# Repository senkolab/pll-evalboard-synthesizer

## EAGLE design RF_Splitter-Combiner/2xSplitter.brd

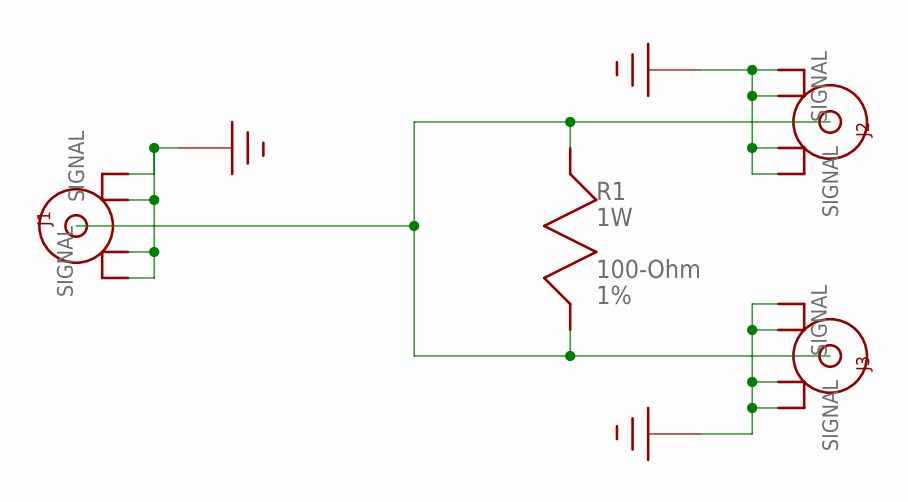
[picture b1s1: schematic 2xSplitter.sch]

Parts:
J1, J2, J3: SMA-END
R1: 100-Ohm; R1206

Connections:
GROUND: J1.P$2, J1.P$3, J1.P$4, J1.P$5, J2.P$2, J2.P$3, J2.P$4, J2.P$5, J3.P$2, J3.P$3, J3.P$4, J3.P$5
unnamed: J1.SIGNAL, J2.SIGNAL, J3.SIGNAL, R1.P$1 (A), R1.P$2 (B)

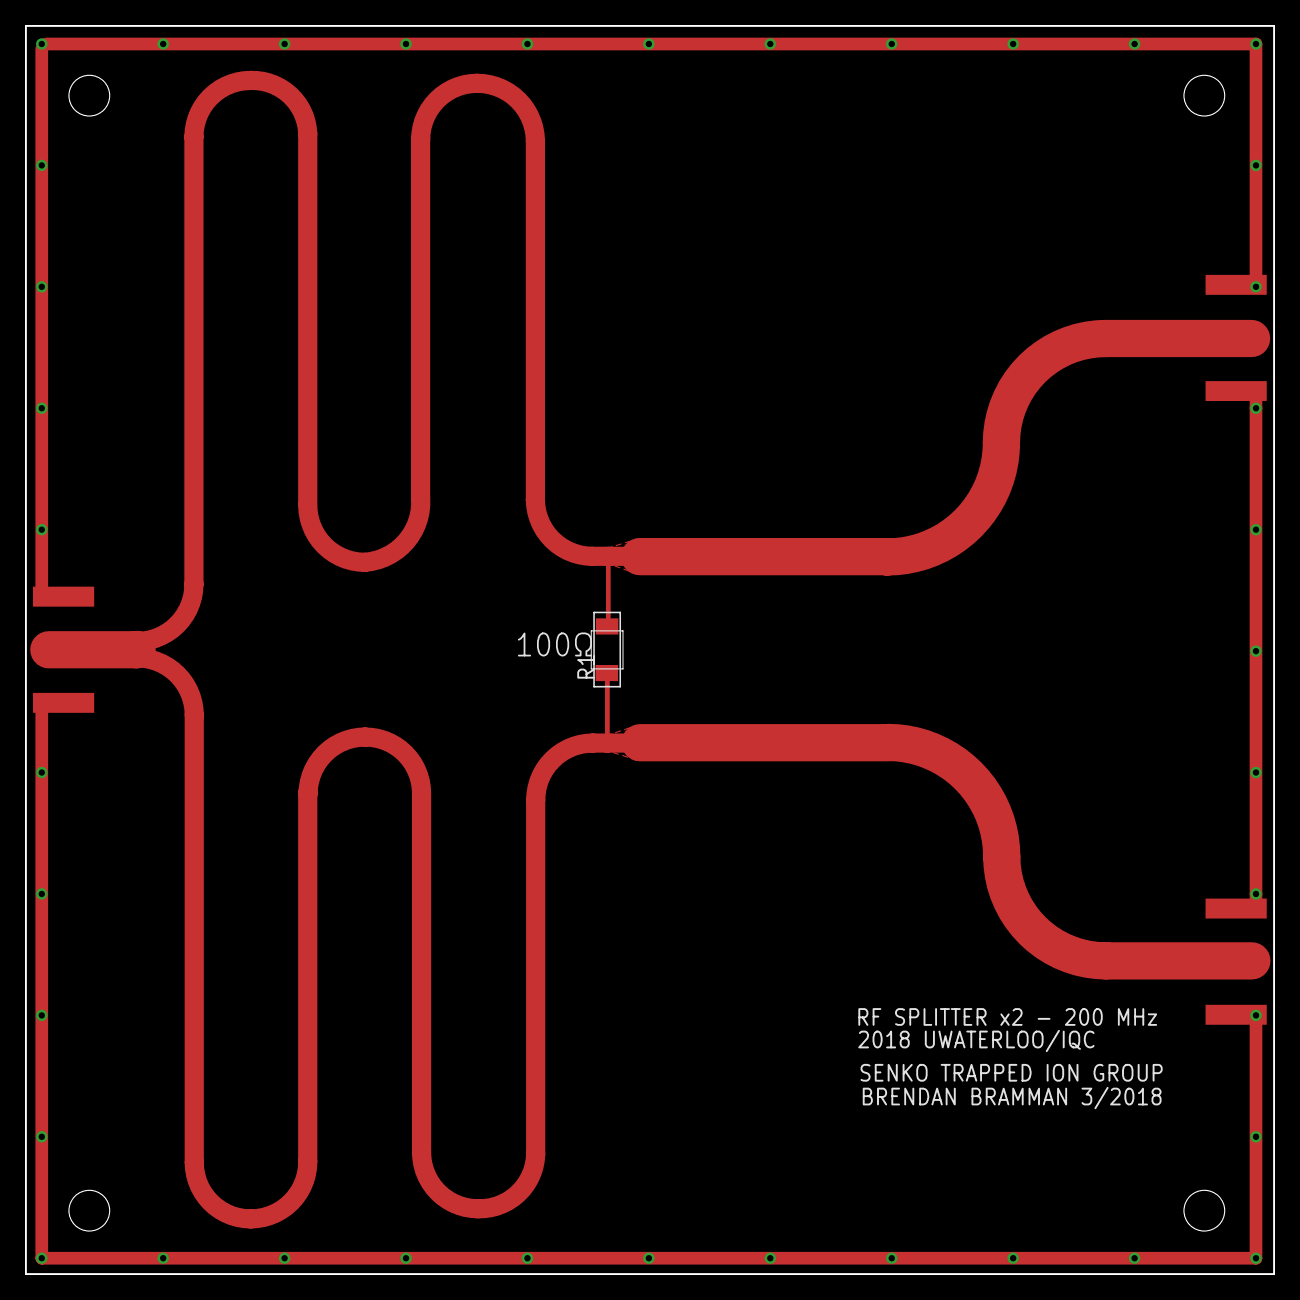
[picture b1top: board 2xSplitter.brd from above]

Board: 2 copper layers, 100.0 x 100.0 mm, 4 parts (0 on the bottom side), 2 nets.

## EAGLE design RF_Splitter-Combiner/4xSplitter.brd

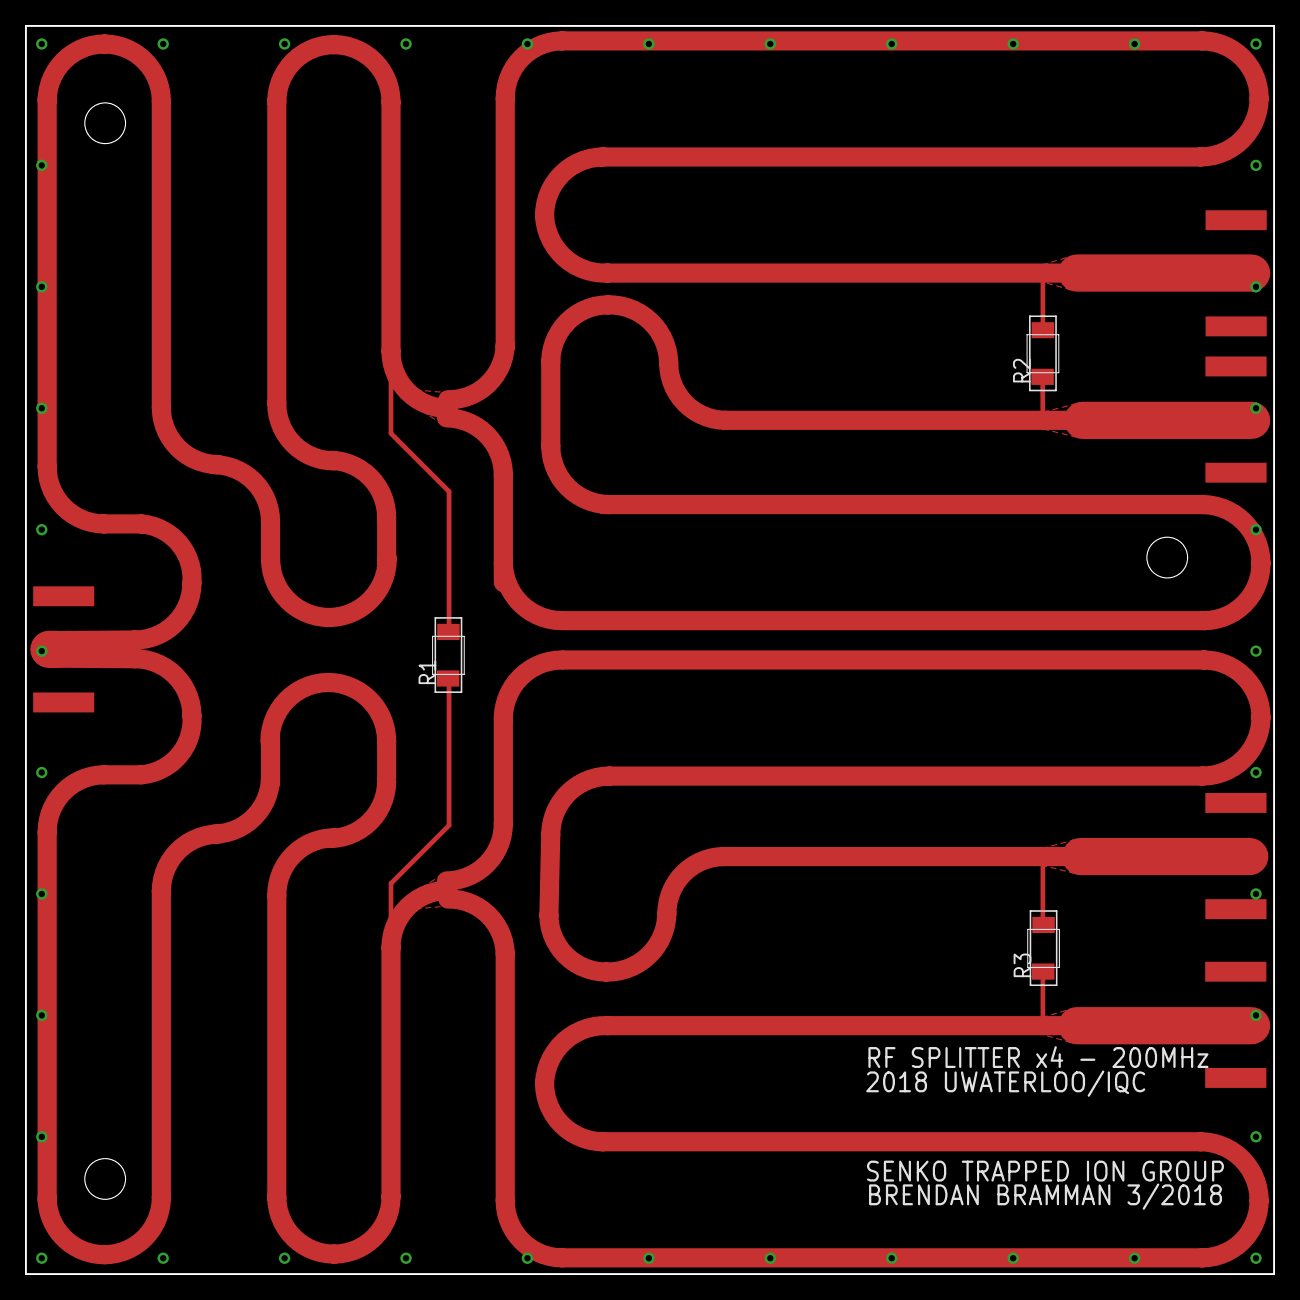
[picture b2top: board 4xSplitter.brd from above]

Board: 2 copper layers, 100.0 x 100.0 mm, 8 parts (0 on the bottom side), 2 nets.

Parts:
J1, J2, J3, J4, J5: SMA-END
R1, R2, R3: 100 - Ohm; R1206

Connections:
GROUND: J1.P$2, J1.P$3, J1.P$4, J1.P$5, J2.P$2, J2.P$3, J2.P$4, J2.P$5, J3.P$2, J3.P$3, J3.P$4, J3.P$5, J4.P$2, J4.P$3, J4.P$4, J4.P$5, J5.P$2, J5.P$3, J5.P$4, J5.P$5
unnamed: J1.SIGNAL, J2.SIGNAL, J3.SIGNAL, J4.SIGNAL, J5.SIGNAL, R1.P$1, R1.P$2, R2.P$1, R2.P$2, R3.P$1, R3.P$2

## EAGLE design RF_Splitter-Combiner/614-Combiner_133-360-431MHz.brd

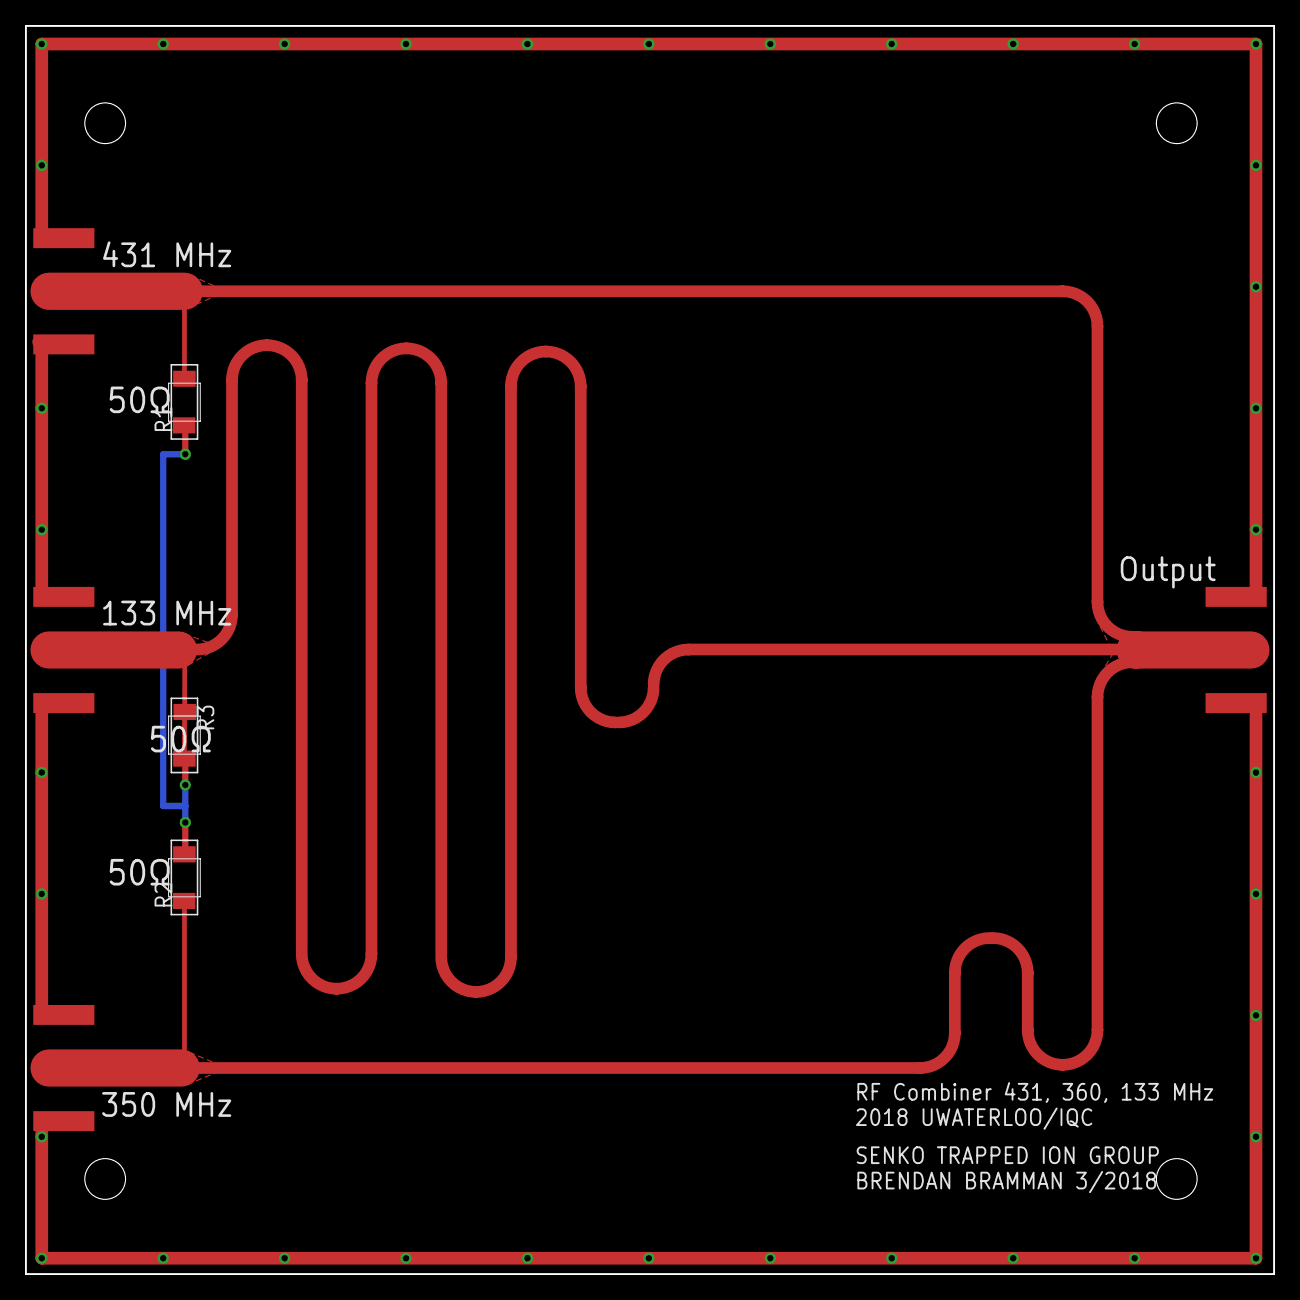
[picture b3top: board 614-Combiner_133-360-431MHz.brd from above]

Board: 2 copper layers, 100.0 x 100.0 mm, 7 parts (0 on the bottom side), 2 nets.

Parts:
J1, J2, J3, J4: SMA-END
R1, R2, R3: 50 Ohm; R1206

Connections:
GROUND: J1.P$2, J1.P$3, J1.P$4, J1.P$5, J2.P$2, J2.P$3, J2.P$4, J2.P$5, J3.P$2, J3.P$3, J3.P$4, J3.P$5, J4.P$2, J4.P$3, J4.P$4, J4.P$5
unnamed: J1.SIGNAL, J2.SIGNAL, J3.SIGNAL, J4.SIGNAL, R1.P$1, R1.P$2, R2.P$1, R2.P$2, R3.P$1, R3.P$2

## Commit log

2018-01-01 Initial System Description.docx and datasheets.
2018-01-02 Updated Basic Bringup of PLL.docx with results of experiments
2018-01-02 added basic mechanical models for each board. Prep for box design
2018-01-03 updates to documentation
2018-01-03 added adf4355-2.py
2018-01-03 Added spi-test.py
2018-01-03 updates to adf4355-2.py
2018-01-03 rename adf4355-2.py to adf4355_2.py due to python naming issues
2018-01-03 added encoding to adf4355_2.py
2018-01-03 bug fixes for syntax in adf4355_2.py
2018-01-03 updated adf4355_2.py
2018-01-03 added adf41020.py, refactored changes to adf4355_2.py
2018-01-04 added pll_program.py. added capability to program from ADF41020 object
2018-01-04 added startup script
2018-01-05 test for tortoisegit
2018-01-05 fixed some empty registers
2018-01-05 Checkin of production version of files
2018-01-05 added a new voltage regulator 1965fb.pdf
2018-01-05 Simulation of Voltage Supplies
2018-01-08 updated with loop command line feature
2018-01-09 New 5.5v power supply added
2018-01-21 added all 4
2018-03-06 added adf41020.py
2018-03-07 a simple client and server
2018-03-08 Initial testing of ADF4355-2 board
2018-03-08 Set reserved bits in encodings...verified with GUI screenshot
2018-03-08 successful test of most frequency tunes
2018-03-08 add gitignore
2018-03-08 put all pllboard class into one file
2018-03-08 make unify interface for both pllboard
2018-03-08 update server for error handling
2018-03-08 update
    - python3 compatiable
    - test socket connection
2018-03-09 updated missing definition in decode_registers function of adf4355_2.py
2018-03-09 first version of GUI
2018-03-09 implement socket connection for GUI client
2018-03-09 update a better GUI
2018-03-09 Make it scalable for adding channel in the panel in the future
2018-03-09 bug fixed
2018-03-15 Synthesizer Box Diagram
2018-03-16 Edited Synthbox
2018-04-06 Splitters/Combiners
2018-04-06 Organized - Added Splitter-Design Documentation
2018-04-09 CADs of PCBs created
2018-04-12 Power Reg
2018-04-23 adf4360 Code created
2018-04-27 asdf
2018-05-01 Add rack Inventor File
2018-05-11 Attenuator Code
2018-05-16 GPIO
2018-05-16 Test for GPIO, Edit ADF4360-8
2018-05-17 Attenuator test created, LatchEnable file created
2018-05-18 Got all programs working
2018-05-18 Fix ADF41020
2018-05-18 adf41020
2018-05-18 Latch enable works for all devices now.
2018-06-08 Fixed attenuator code
    X
2018-06-13 Documentation for multi-device control
2018-06-27 Got attenuator working with multiple ADF4355 boards
2018-06-27 CAD files updated
2018-06-27 Moved things around
2018-06-29 Organization of classes - JSON configuration setup
2018-07-05 Changed adf41020 test to use attenuator as well
2018-07-05 Add printing to adf41020 Test
2018-08-26 Switch Panel dividers
2018-08-31 No more output B for adf4355, and LE handling is now within pe4312 class
2018-08-31 No loop for PE4312 test
2018-09-05 Name Change
2018-09-13 Documentation and PLL Diagram updated
2018-09-13 Update Documentation
2018-09-13 Documentation
2018-09-14 Got adf41020 working again - polarity negative
2018-09-24 Holder for Raspberry Pi Cables
2019-01-30 Documentation of PLLs
2019-02-06 Created fan holder and bracket to hold ilando boards. Updated frequency sources diagram
2019-02-12 Completely up to date source code for PLL control
2019-04-05 Documentation added, test functions changed
2019-04-05 Cleaned up program files for PLL testing
2019-04-11 Some documentation added
2019-07-11 Added sweeping capabilities for pll
2019-07-19 Made final program folder, made triple arguments option, changed names from "test_"
2019-08-06 Added Nigel's controller code - can control all raspberry pi's from one computer
2019-08-06 Added command line arg capabilities for sweep and mw
2019-08-07 Update PLL_Controller.py
    Updated functions to work with Brendan's new code. Bug fixes.
2019-08-07 Sweep Changes / Bug Fixes
    Fixed erros in the frequency sweep code.
2019-08-07 Fixed sweep Please enter the commit message for your changes. Lines starting
2019-08-07 Frequency Setting
    Updated CLI with ability to change frequency of the AOMs associated with the 650nm and 493nm lasers. Untested.
2019-08-07 Update PLL_Controller.py
    Bug fixes, updated display commands and docstrings.
2019-08-07 Update PLL_Controller.py
    Updated to include frequency sweeping capabilities. Untested.
2019-08-23 Update rf1.py
    Bufixing command line arguments
2019-08-23 Ease of use updates
    Added units for CLI, changed units to command line argument inputs for sweeping to MHz from Hz
2019-08-23 Bugfix PLL_Controller.py
    Fixed bugs in sweeping code, now sweeps.
2019-08-23 Update PLL_Controller.py
    Removed debugging sprint statements, lowered fastest allowed sweep time to 0.5s
2019-08-23 Update PLL_Controller.py
    Bug fix. Added automatic connect to pi3 on start.
2019-08-23 Update PLL_Controller.py
    Updated help.
2019-11-25 Added Isotope switching diagrams
    Updated help.
2019-11-28 Updated isotope switching diagram
    Changed 650nm laser to be 200MHz off resonant so that we can discriminate between Ba138 and other isotopes - all frequencies for 650nm are now 200MHz different from before.
2020-01-06 Added Usman's updated isotope switching diagram
2020-02-03 New diagram made for printout and tape to shelves
2020-03-04 Added Pifreqs and Pipowers
2020-03-04 Added Pi5Freqs Pi5Powers
2020-03-04 Added Pi2Freqs Pi2Powers
2020-03-04 Made Freqs Powers in folders
2020-03-04 Added Pi4 folder
2020-03-04 Added Pi3 folders for Freqs, Powers
2020-03-04 Changed Freq, Power files to point to correct place
2020-03-06 Made isotope switching diagrams with different frq offsets
2020-03-06 Auto stash before merge of "master" and "origin/master"
2020-03-06 Deleted extra files
2021-02-08 Moved documentation around a bit
